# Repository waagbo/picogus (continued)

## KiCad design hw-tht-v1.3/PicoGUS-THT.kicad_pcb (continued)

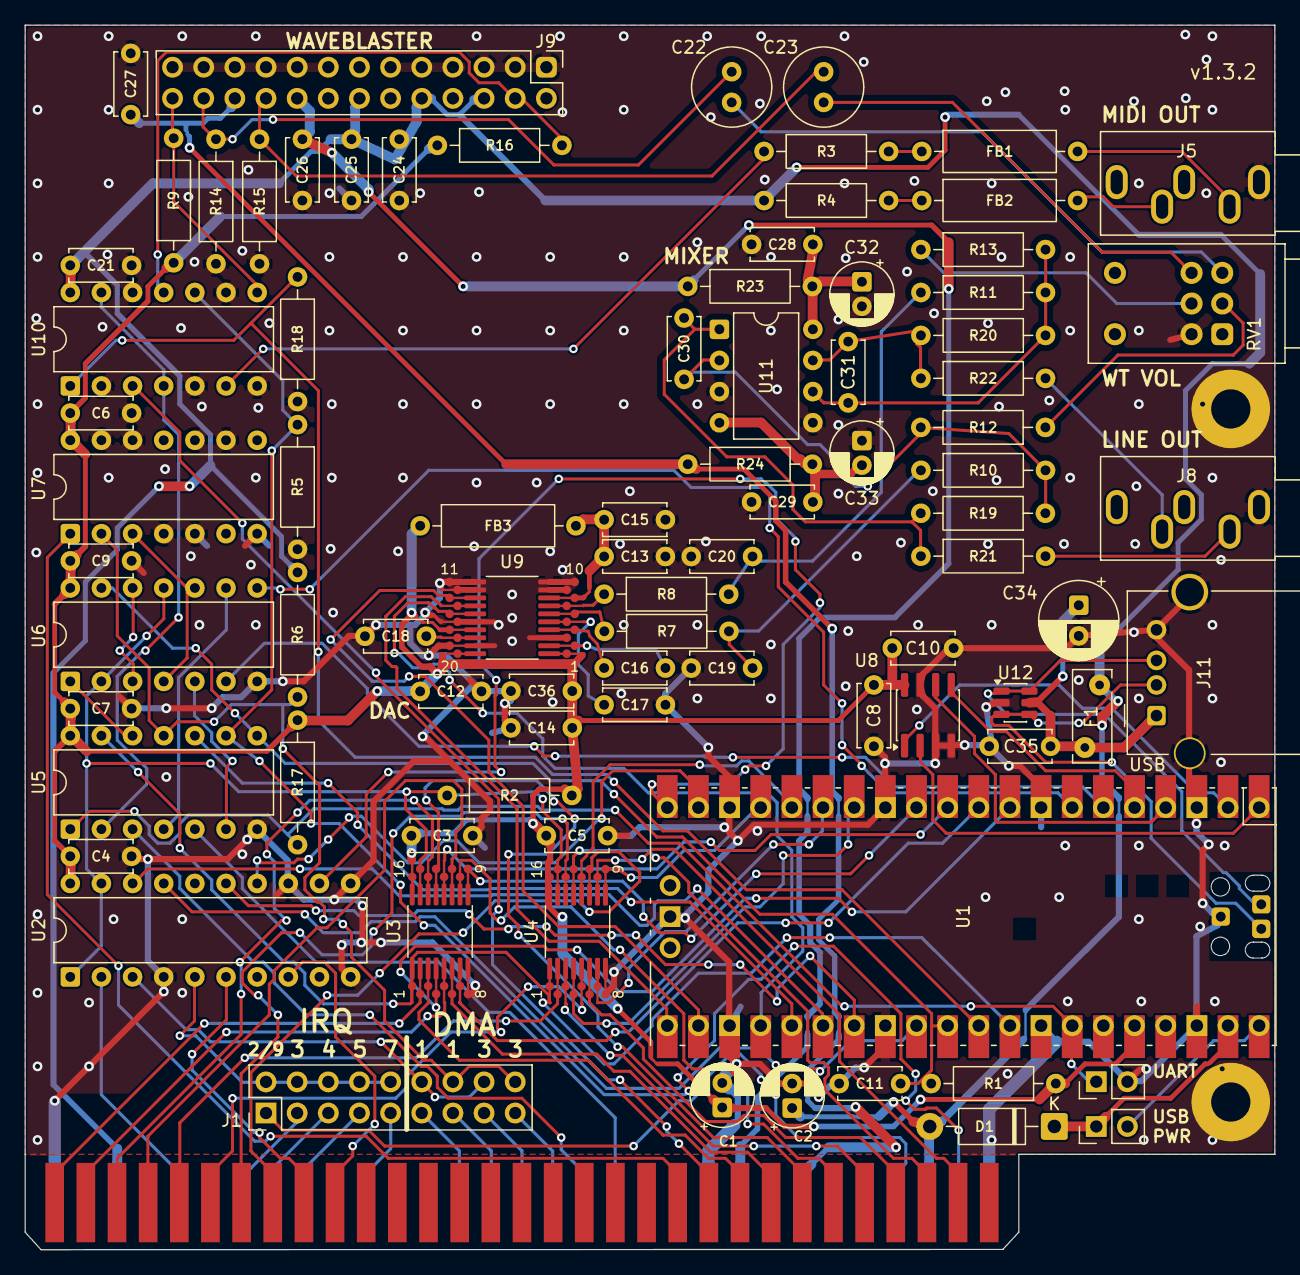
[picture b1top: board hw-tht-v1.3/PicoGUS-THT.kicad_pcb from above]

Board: 2 copper layers, 101.9 x 99.8 mm, 88 parts (0 on the bottom side), 110 nets.

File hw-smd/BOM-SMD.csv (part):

References,Qty,Value,Type,Footprint,Manufacturer,MPN,DigiKey PN,DigiKey link,DigiKey stock 2026-09-29,Unit NOK (1 board),Line NOK (1 board),Alternatives,Notes
U1,1,Raspberry Pi Pico,THT module,RPi_Pico_SMD_TH,Raspberry Pi,SC0915,2648-SC0915CT-ND,https://www.digikey.no/no/products/result?keywords=2648-SC0915CT-ND,42851,44.05,44.05,"Pico H SC0917 (DK 2648-SC0917-ND, 8889; JLCPCB lib C21351132). Pico W also works.","LCSC: Pico is only in the JLCPCB assembly parts library, not the LCSC shop - buy from DigiKey or an approved Raspberry Pi reseller. Solder on 2x 1x20 male headers (from the 1x40 strip) or socket it."
U2,1,74LVC244,SMD TSSOP-20,TSSOP-20_4.4x6.5mm_P0.65mm,Texas Instruments,SN74LVC244APW,296-26609-5-ND,https://www.digikey.no/no/products/result?keywords=296-26609-5-ND,2154,11.61,11.61,"Nexperia 74LVC244APW,118 (v1.2 BOM, DK 1727-2875-1-ND, 0 in stock today).",
"U3, U4",2,SN74CB3T3257,SMD TSSOP-16,TSSOP-16_4.4x5mm_P0.65mm,Texas Instruments,SN74CB3T3257PWR,296-17850-1-ND,https://www.digikey.no/no/products/result?keywords=296-17850-1-ND,4031,19.96,39.93,,TSSOP-16. No DIP or SOIC version exists (only PW/DGV).
U5,1,74AHC14,SMD SOIC-14,SOIC-14_3.9x8.7mm_P1.27mm,Diodes Inc,74AHC14S14-13,31-74AHC14S14-13CT-ND,https://www.digikey.no/no/products/result?keywords=31-74AHC1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,3070,3.55,3.55,,"Must be 74AHC14 (higher Schmitt threshold, see v1.2 changelog)."
U6,1,74LVC00,SMD SOIC-14,SOIC-14_3.9x8.7mm_P1.27mm,Diodes Inc,74LVC00AS14-13,31-74LVC00AS14-13CT-ND,https://www.digikey.no/no/products/result?keywords=31-74LVC0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,1816,3.65,3.65,,
U7,1,74LVC1G00,SMD SOT-23-5,SOT-23-5,Texas Instruments,SN74LVC1G00DBVR,296-9845-1-ND,https://www.digikey.no/no/products/result?keywords=296-9845-1-ND,14500,1.34,1.34,,
U8,1,APS6404L-3SQR-SN,SMD SOIC-8,SOIC-8_3.9x4.9mm_P1.27mm,AP Memory,APS6404L-3SQR-SN [Adafruit 4677 (64Mbit QSPI PSRAM)],1528-4677-ND,https://www.digikey.no/no/products/result?keywords=1528-4677-ND,4132,16.80,16.80,,SOIC-8. DigiKey does not stock the APS6404L itself; Adafruit 4677 is the DigiKey source (as in v1.2). Note: v1.2 BOM LCSC C139966 is actually a Vilsion VTI7064MSME (compatible).
U9,1,PCM5100A,SMD TSSOP-20,TSSOP-20_4.4x6.5mm_P0.65mm,Texas Instruments,PCM5100APWR,296-36705-1-ND,https://www.digikey.no/no/products/result?keywords=296-36705-1-ND,1419,25.15,25.15,"Pin-compatible PCM5102APWR (DK 296-36707-1-ND 619, LCSC C107671 6471) or PCM5101APWR.","TSSOP-20, no THT version exists. DAC AREA: leave out U9, C12-C20, FB3, R7 and R8 when the GY-PCM5102 module (J10) is fitted instead."
J10,1,GY-PCM5102 module,"THT (optional, instead of the DAC area)",GY-PCM5102_Module,generic,GY-PCM5102,,,,,,,"OPTION: replaces U9 + C12-C20 + FB3 + R7/R8 - exactly the parts under the dashed J10 module outline (the module has the same 470R/2.2nF output filter). Fit ONE of the two, never both. Not sold by DigiKey (AliExpress/eBay etc). Solder it almost flat, directly on 2.54 mm male pins: its 6-pin I2S header and a 4-pin piece of the 1x40 strip on AGND/ROUT/AGND/LROUT. No sockets: raised on 8.5 mm sockets it would hit a Waveblaster daughterboard. Set its solder jumpers H1=L H2=L H3=H H4=L."
"U10, U12",2,74LVC2G06,SMD SOT-23-6,TSOP-6_1.65x3.05mm_P0.95mm,Texas Instruments,SN74LVC2G06DBVR,296-13492-1-ND,https://www.digikey.no/no/products/result?keywords=296-13492-1-ND,25644,3.46,6.91,,Open-drain inverters. U10: IOCHRDY + MIDI out (as v1.2). U12: Waveblaster /RESET + MIDI (new).
U11,1,NE5532,SMD SOIC-8,SOIC-8_3.9x4.9mm_P1.27mm,Texas Instruments,NE5532DR,296-13622-1-ND,https://www.digikey.no/no/products/result?keywords=296-13622-1-ND,50117,4.80,4.80,,WT/PCM summing amplifier on the (filtered) ISA +/-12 V.
D1,1,B5819W,SMD SOD-123,D_SOD-123,Slkor (Shenzhen Slkormicro),B5819W,5399-B5819WCT-ND,https://www.digikey.no/no/products/result?keywords=5399-B5819WCT-ND,67294,2.69,2.69,,"40 V 1 A Schottky, SOD-123 (cut tape; 5399-B5819WTR-ND is a 3000-pc reel). Replaces MCC B5819W-TP (purchase-limited at DigiKey); Comchip CDBW140-G (641-1458-1-ND) also fits. JLCPCB assembly keeps B5819W (LCSC C84354)."
"C1, C2",2,47uF,SMD 1206,C_1206_3216Metric,TDK,C3216X5R1A476M160AB,445-6006-1-ND,https://www.digikey.no/no/products/result?keywords=445-6006-1-ND,33669,7.97,15.93,v1.2 Samsung CL31A476MPHNNNE (0 at DigiKey today).,
"C3, C4, C5, C6, C7, C8, C9, C11, C12, C13, C14, C18, C21, C25, C26, C27, C28, C29",18,0.1uF,SMD 0805,C_0805_2012Metric,Samsung,CL21B104KBCNNNC,1276-1003-1-ND,https://www.digikey.no/no/products/result?keywords=1276-1003-1-ND,4889645,0.43,7.77,,50V X7R.
C10,1,1uF,SMD 0805,C_0805_2012Metric,TDK,C2012X7R1H105K125AB,445-7547-1-ND,https://www.digikey.no/no/products/result?keywords=445-7547-1-ND,7594,2.88,2.88,,50V X7R.
"C15, C24",2,10uF,SMD 1206,C_1206_3216Metric,Samsung,CL31A106KAHNNNE,1276-1075-1-ND,https://www.digikey.no/no/products/result?keywords=1276-1075-1-ND,18634,2.11,4.22,"TDK C3216X5R1E106K160AB (DK 445-6862-1-ND, 43950).",25V X5R. 1206 because no 10uF 0805 is in stock at DigiKey today.
"C16, C17",2,2.2uF,SMD 0805,C_0805_2012Metric,TDK,C2012X7R1H225K125AC,445-5968-1-ND,https://www.digikey.no/no/products/result?keywords=445-5968-1-ND,499706,5.09,10.17,,50V X7R.
"C19, C20",2,2.2nF C0G,SMD 0805,C_0805_2012Metric,Samsung,CL21C222JBFNNNE,1276-2993-1-ND,https://www.digikey.no/no/products/result?keywords=1276-2993-1-ND,51757,1.34,2.69,,C0G/NP0 (DAC output filter). DAC AREA: leave out with the GY-PCM5102 module (J10).
"C30, C31",2,47pF C0G,SMD 0805,C_0805_2012Metric,Samsung,CL21C470JC61PNC,1276-6521-1-ND,https://www.digikey.no/no/products/result?keywords=1276-6521-1-ND,67127,1.70,3.40,,"C0G/NP0 (op-amp feedback), 100 V. Previous value: 100pF C0G (Samsung CL21C101JBANNNC). 47 pF with the 20k feedback keeps the feedback pole at ~170 kHz. JLCPCB/LCSC: C14857 (CL21C470JBANNNC, 50 V; DigiKey does not stock it). Stock checked 2026-10-09."
"C22, C23",2,10uF bipolar,SMD 6.3x5.4,CP_Elec_6.3x5.4,Panasonic,EEE-1EA100NP,PCE4294CT-ND,https://www.digikey.no/no/products/result?keywords=PCE4294CT-ND,6070,6.05,12.09,"Nichicon UUP1V100MCL1GS (bipolar 35V, DK 493-9559-1-ND, 3792).",WT audio coupling: NON-POLAR electrolytic (either orientation). The footprint shows a + mark only because KiCad has no non-polar SMD electrolytic footprint.
"C32, C33",2,47uF 35V,SMD 6.3x7.7,CP_Elec_6.3x7.7,Panasonic,EEE-FK1V470P,PCE3842CT-ND,https://www.digikey.no/no/products/result?keywords=PCE3842CT-ND,47922,6.24,12.48,,Op-amp +/-12 V RC filter. C33: + to GND.
"FB1, FB2, FB3",3,1k@100MHz,SMD 0805,L_0805_2012Metric,Murata,BLM21AG102SN1D,490-1041-1-ND,https://www.digikey.no/no/products/result?keywords=490-1041-1-ND,621156,1.54,4.61,,FB1/FB2: MIDI out EMI. FB3: DAC AVDD filter.
R1,1,1k,SMD 0805,R_0805_2012Metric,Yageo,RC0805FR-071KL,311-1.00KCRCT-ND,https://www.digikey.no/no/products/result?keywords=311-1.00KCRCT-ND,732526,0.96,0.96,,
"R2, R5, R6",3,15k,SMD 0805,R_0805_2012Metric,Yageo,RC0805FR-0715KL,311-15.0KCRCT-ND,https://www.digikey.no/no/products/result?keywords=311-15.0KCRCT-ND,127426,0.96,2.88,,
"R3, R4",2,220R,SMD 0805,R_0805_2012Metric,Yageo,RC0805FR-07220RL,311-220CRCT-ND,https://www.digikey.no/no/products/result?keywords=311-220CRCT-ND,420320,0.96,1.92,,
"R7, R8",2,470R 0.1% thin film,SMD 0805,R_0805_2012Metric,Yageo,RT0805BRD07470RL,YAG1904CT-ND,https://www.digikey.no/no/products/result?keywords=YAG1904CT-ND,12924,1.06,2.11,,"Thin film in the audio path (lower noise and voltage coefficient than thick film). DAC output filter: leave out with the GY-PCM5102 module (J10), which has the same filter."
"R12, R13",2,10k 0.1% thin film,SMD 0805,R_0805_2012Metric,Yageo,RT0805BRD0710KL,YAG1763CT-ND,https://www.digikey.no/no/products/result?keywords=YAG1763CT-ND,176155,0.96,1.92,,"Mixer WT inputs: thin film, 0.1% keeps the L/R gains matched. Until 2026-10-09 this line also held R10, R11, R19, R20 (6 pcs); those are now 20k."
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
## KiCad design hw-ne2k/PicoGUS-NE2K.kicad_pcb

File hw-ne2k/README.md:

# PicoGUS NE2000 v1.0 – WiFi network card based on PicoGUS v1.2

A third card in this repository: the PicoGUS **v1.2** ISA interface with **everything audio removed**,
built around a **Raspberry Pi Pico W** so it runs the PicoGUS NE2000 firmware (`pg-ne2k`: an NE2000
that talks to the network over WiFi). Added:

* **USB-A host port** at the bracket, wired to the Pico W's USB test points (TP2/TP3), for USB mice,
  joysticks and storage (the same idea as the PicoGUS 2.0 USB-A port)
* **8 MB PSRAM** (APS6404L) kept, for buffering/caching in future firmware
* **Boot ROM** on the ISA memory bus: an in-system-writable SST39SF010A flash with 4 × 32 KB images
  (e.g. iPXE for PXE boot, a disk-image boot ROM, XT-IDE BIOS), configured from the Pico W

> **Status: prototype design, not yet fabricated or tested.** The schematic passes ERC (no errors
> beyond those inherited from v1.2). The board was autorouted and checked with DRC in KiCad 10:
> **0 errors, 0 unconnected**, and it matches the schematic. Firmware support for the boot ROM
> (enable/base/bank set-up, ROM images, flashing tool) does not exist yet; the stock `pg-ne2k` firmware
> runs the NE2000 and leaves the ROM switched off.

| File | What |
|---|---|
| `PicoGUS-NE2K.kicad_pro/.kicad_sch/.kicad_pcb` | KiCad **10** project. Root sheet: the v1.2 ISA logic + Pico W + PSRAM |
| `bootrom.kicad_sch` | Boot ROM (U13–U16) and USB-A host port (J5, U17, F1) |
| `PicoGUS-NE2K-schematic.pdf` | Schematic PDF |
| `BOM-NE2K.csv` | BOM with a **DigiKey link** for every line, stock and NOK price |
| `BOM-NE2K-digikey-upload.csv` / `-10x.csv` | DigiKey cart/BOM upload for 1 / 10 boards (designators as Customer Reference) |
| `build/jlcpcb/` | Gerbers, drill, assembly BOM and placement files for JLCPCB (regenerate with `hw-common/tools/jlcpcb.sh`) |

## What is on the card

### Kept from v1.2 (unchanged)

U2 74LVC244, U3/U4 SN74CB3T3257, U5 74AHC14, U6 74LVC00, U7 74LVC1G00, U8 APS6404L PSRAM and
U10A 74LVC2G06 (IOCHRDY), with the same Pico GPIO assignment as v1.2. So the stock PicoGUS firmware
builds (`pg-ne2k`, the USB mouse/joystick build, `multifw`) work without changes; the sound modes of
`multifw` simply have no DAC to play through.

### Removed

* **Audio:** PCM510x DAC, the GY-PCM5102 option, line-out and the Waveblaster/mixer section of v1.3
* **MIDI out** (J5 jack, R3/R4, FB1/FB2). U10B stays on the board (its input is still driven) with the
  output unconnected.
* **ISA DMA:** the DRQ/DACK jumpers and the DRQ/DACK/TC paths. The NE2000 moves packet data with
  programmed I/O through its data port (its "remote DMA" is internal to the NE2000, not ISA DMA), so
  `pg-ne2k` never uses DRQ or DACK. DACK keeps its pull-up (R6), so the AEN gating (U7) works as before.
* **J7 (USB power jumper):** the USB-A port has its own VBUS supply.

### IRQ (J1)

J1 is now a **2×5 header**: one jumper selects **IRQ 2/9, 3, 4, 5 or 7** for the NE2000 (same layout as
the IRQ half of the v1.2 J1). IRQ 3 is the usual NE2000 choice if COM2 is not used.

### Pico W, antenna and USB-A

* **U1 must be a Pico W** (SC0918). The NE2000 firmware is built for the RP2040 + CYW43439; a
  Pico 2 W does not work.
* **Solder the Pico W flat** (castellated edges, or pins cut flush), not on header pins: the USB data
  lines are taken from its **TP2 (D−) and TP3 (D+)** test points on the underside. The footprint
  (`RPi_PicoW_SMD_TH_USB`) has plated 1.5 mm pads with a 0.6 mm hole there, so you solder them from the
  back of the card after the module is in place. TP1 (USB ground) is connected the same way. A Pico WH
  (pre-soldered headers) cannot be used.
* **The antenna end points at the bracket**, as far out as the board allows. No copper on either layer
  under the antenna (datasheet keep-out, 14 × 9 mm between the pin rows) or between the module end and
  the bracket edge. The footprint also drops the Pico's SWD pads, which would sit under the Pico W
  antenna.
* **USB-A (J5, Molex 67643)** sits at the bracket below the antenna, on the line of the v1.2 line-out jack.
  D+/D− run straight from the Pico's test points (the Pico's own 27 Ω series resistors are before them),
  with a USBLC6-2SC6 ESD protector (U17). VBUS comes from the ISA +5 V through a 0.5 A polyfuse (F1)
  with 10 µF + 0.1 µF. The Pico's own VBUS pin is not connected, so a PC on the micro-USB port (on the
  bench, for flashing) and the ISA supply never feed each other.
* **Firmware updates** go over ISA with `pgusinit` as usual. The micro-USB socket now faces into the card;
  it is still usable with the card out of the PC (BOOTSEL on the Pico).

### Boot ROM (bootrom.kicad_sch)

A real option ROM on the ISA memory bus, so the BIOS finds and runs it during POST.

* **U13 SST39SF010A** (128 KB, 5 V, PLCC-32), read through a **32 KB window**: SA0–SA14 go straight to the
  flash. Flash A15/A16 are the **bank** bits from the Pico, so the chip holds **4 images of 32 KB**.
* **U14 74HCT688** compares SA19..SA15 with `1 1 BASE2 BASE1 BASE0` and requires **ROM_EN = 1**. Its
  enable is `~MEMSTB` (U16: low during any ISA memory read or write), so the output `~ROM_CS` is only
  active in a memory cycle inside the window.
* **U15 74AHCT245** drives the flash data onto the ISA data bus (the flash alone is too weak for a loaded
  bus). Direction comes from `~SMEMW`, enable from `~ROM_CS`.
* **Base address** (BASE2..0): `001` C8000, `010` D0000, `011` D8000, `100` E0000, `101` E8000.
* **ROM_EN, BASE0–2, BANK0–1 are Pico GPIOs** (the pins freed by removing I2S and DMA):

  | GPIO | Pico pin | Signal |
  |---|---|---|
  | 16 | 21 | ROM_EN (pulled low by R3: ROM off until the firmware enables it) |
  | 17 | 22 | ROM_BASE0 |
  | 18 | 24 | ROM_BASE1 |
  | 19 | 25 | ROM_BASE2 |
  | 20 | 26 | ROM_BANK0 |
  | 22 | 29 | ROM_BANK1 |

  The firmware should set them from its stored settings first thing after reset. The Pico is running
  within tens of milliseconds of ISA RESET, while the BIOS scans for option ROMs only after its memory
  test. With the stock firmware the ROM stays invisible.
* **Writing the ROM from DOS:** fit **J2** (write enable: `~SMEMW` → flash WE#, R4 holds WE# high
  otherwise), then use the SST software command sequence (5555h/2AAAh lie inside the 32 KB window).
  Remove J2 afterwards.
* **What to put in the banks:** iPXE built with its `ne2k_isa` driver (PXE boot; iPXE needs a 386 or
  later), a small INT 13h ROM that boots a disk image the Pico fetches over WiFi (cached in the PSRAM; works
  on an 8088), or an XT-IDE BIOS. All of this is firmware work; the hardware only provides the ROM.

## Card dimensions and bracket

The card uses the **v1.2 outline: 103.7 × 74.2 mm** (bracket edge to far edge × fingers to top), with the
v1.2 edge connector and bracket holes H1/H2, so a v1.2 bracket screws on. The bracket needs:

* a **large opening in front of the antenna** (around the old MIDI-jack hole, y ≈ 80 mm on the board):
  metal close to the antenna is what costs range,
* a **USB-A cut-out** (about 14 × 7 mm) centred on the old line-out jack hole.

### Silkscreen

Front: IRQ numbers at J1, `ROM WE` at J2, `TX GND` at J6, `USB`, `WiFi ANTENNA` at the antenna end,
`REAR >`. Back: the PicoGUS artwork (`hw-common/art/picogus-artwork.svg`, 70 × 25 mm) over the lower half,
the dedication *This version is dedicated to Mila and Alisa, my two wonderful princesses, who fill my
world with joy.* behind the Pico, and the copyright/licence text (CERN-OHL-P v2).

## Building it

* Everything except U1, J1, J2, J5, J6 and the jumpers is SMD on the top side. `hw-common/tools/jlcpcb.sh
  hw-ne2k/PicoGUS-NE2K.kicad_pcb` writes gerbers, drill, assembly BOM and placement files to `build/jlcpcb/`
  (38 SMD placements). The parts have no LCSC numbers yet, so pick them in JLCPCB's part matcher (or order
  the parts from DigiKey and assemble by hand).
* Solder the **Pico W flat**, then solder **TP1, TP2, TP3 from the back** through the plated holes.
* Jumpers: one on J1 (IRQ). J2 only while writing the boot ROM.
* Firmware: flash `pg-ne2k` (or `multifw`) with `pgusinit`, then set the WiFi SSID/password and the NE2000
  base port with `pgusinit` as on any PicoGUS.

## Ordering

`BOM-NE2K.csv` lists a DigiKey part for every line with stock and price (new parts checked on
digikey.com on 2026-10-05; parts shared with the SMD board from its 2026-09-29 check).
DigiKey parts only (no PCB, no shipping): **about 264 kr excl. MVA (~330 kr incl. 25 % MVA, ~$28) per
board**; the Pico W (73 kr), the PLCC flash (19 kr), the USB-A connector (18 kr) and the two bus switches
(20 kr) are the largest items.

## Sources

* PicoGUS v1.2 schematic (`hw/`) and the v1.3.0 SMD root sheet (`hw-smd/`)
* Raspberry Pi Pico W datasheet (test points TP1–TP6, SMT footprint, antenna keep-out)
* Microchip SST39SF010A datasheet; TI CD74HCT688, SN74AHCT245, SN74AHCT1G08 datasheets
* PicoGUS firmware: `sw/ne2000play.cpp`, `sw/ne2000/ne2000.c`, `sw/CMakeLists.txt` (`NE2K` target)

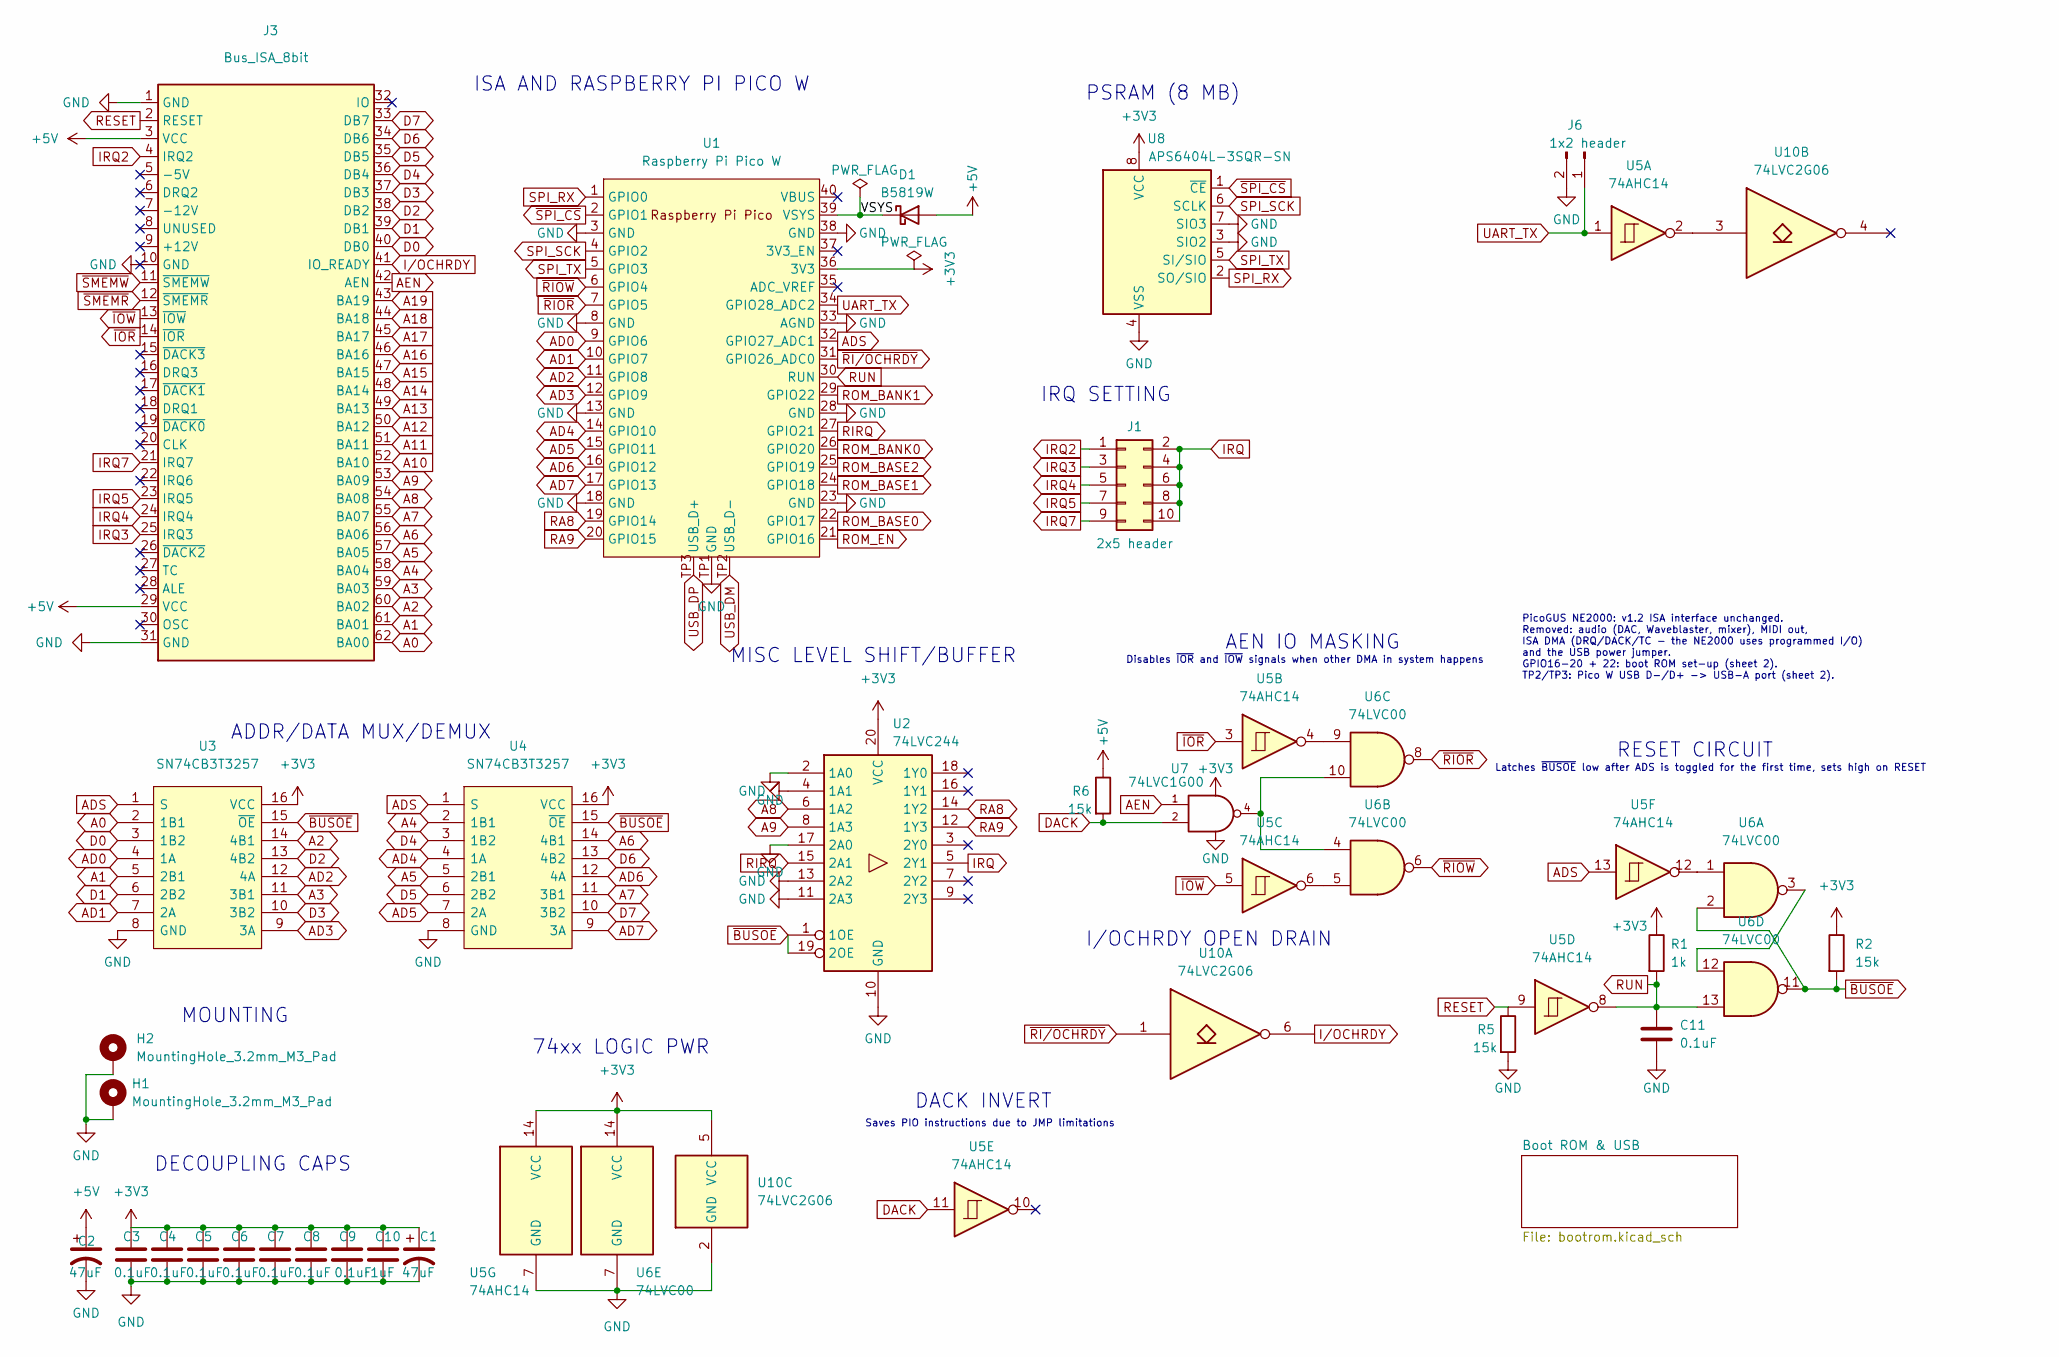
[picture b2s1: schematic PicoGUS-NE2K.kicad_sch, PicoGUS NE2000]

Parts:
C1, C2: 47uF; C_1206_3216Metric; MPN C3216X5R1A476M160AB; DigiKey 445-6006-1-ND
C3, C4, C5, C6, C7, C8, C9, C11: 0.1uF; C_0805_2012Metric; MPN CL21B104KBCNNNC; DigiKey 1276-1003-1-ND
C10: 1uF; C_0805_2012Metric; MPN C2012X7R1H105K125AB; DigiKey 445-7547-1-ND
D1: B5819W; D_SOD-123; MPN B5819W; DigiKey 5399-B5819WCT-ND
H1, H2: MountingHole_3.2mm_M3_Pad
J1: 2x5 header; PinHeader_2x05_P2.54mm_Vertical; MPN 10129381-910001BLF; DigiKey 10129381-910001BLF-ND
J3: Bus_ISA_8bit; BUS_PC_chamfer
J6: 1x2 header; PinHeader_1x02_P2.54mm_Vertical; MPN 77311-118-02LF; DigiKey 609-4434-ND
R1: 1k; R_0805_2012Metric; MPN RC0805FR-071KL; DigiKey 311-1.00KCRCT-ND
R2, R5, R6: 15k; R_0805_2012Metric; MPN RC0805FR-0715KL; DigiKey 311-15.0KCRCT-ND
U1: Raspberry Pi Pico W; RPi_PicoW_SMD_TH_USB; MPN SC0918; DigiKey 2648-SC0918CT-ND
U2: 74LVC244; TSSOP-20_4.4x6.5mm_P0.65mm; MPN SN74LVC244APW; DigiKey 296-26609-5-ND
U3, U4: SN74CB3T3257; TSSOP-16_4.4x5mm_P0.65mm; MPN SN74CB3T3257PWR; DigiKey 296-17850-1-ND
U5: 74AHC14; SOIC-14_3.9x8.7mm_P1.27mm; MPN 74AHC14S14-13; DigiKey 31-74AHC14S14-13CT-ND
U6: 74LVC00; SOIC-14_3.9x8.7mm_P1.27mm; MPN 74LVC00AS14-13; DigiKey 31-74LVC00AS14-13CT-ND
U7: 74LVC1G00; SOT-23-5; MPN SN74LVC1G00DBVR; DigiKey 296-9845-1-ND
U8: APS6404L-3SQR-SN; SOIC-8_3.9x4.9mm_P1.27mm; MPN APS6404L-3SQR-SN; DigiKey 1528-4677-ND
U10: 74LVC2G06; TSOP-6_1.65x3.05mm_P0.95mm; MPN SN74LVC2G06DBVR; DigiKey 296-13492-1-ND

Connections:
+3V3: C1.1, C3.1, C4.1, C5.1, C6.1, C7.1, C8.1, C9.1, C10.1, R1.1, R2.1, U1.36 (3V3), U2.20 (VCC), U3.16 (VCC), U4.16 (VCC), U5.14 (VCC), U6.14 (VCC), U7.5 (VCC), U8.8 (VCC), U10.5 (VCC)
+5V: C2.1, D1.2 (A), J3.3 (VCC), J3.29 (VCC), R6.1; also elsewhere on the board
/VSYS: D1.1 (K), U1.39 (VSYS)
A0: J3.62 (BA00), U3.2 (1B1); also elsewhere on the board
A1: J3.61 (BA01), U3.5 (2B1); also elsewhere on the board
A2: J3.60 (BA02), U3.14 (4B1); also elsewhere on the board
A3: J3.59 (BA03), U3.11 (3B1); also elsewhere on the board
A4: J3.58 (BA04), U4.2 (1B1); also elsewhere on the board
A5: J3.57 (BA05), U4.5 (2B1); also elsewhere on the board
A6: J3.56 (BA06), U4.14 (4B1); also elsewhere on the board
A7: J3.55 (BA07), U4.11 (3B1); also elsewhere on the board
A8: J3.54 (BA08), U2.6 (1A2); also elsewhere on the board
A9: J3.53 (BA09), U2.8 (1A3); also elsewhere on the board
A10: J3.52 (BA10); also elsewhere on the board
A11: J3.51 (BA11); also elsewhere on the board
A12: J3.50 (BA12); also elsewhere on the board
A13: J3.49 (BA13); also elsewhere on the board
A14: J3.48 (BA14); also elsewhere on the board
A15: J3.47 (BA15); also elsewhere on the board
A16: J3.46 (BA16); also elsewhere on the board
A17: J3.45 (BA17); also elsewhere on the board
A18: J3.44 (BA18); also elsewhere on the board
A19: J3.43 (BA19); also elsewhere on the board
AD0: U1.9 (GPIO6), U3.4 (1A)
AD1: U1.10 (GPIO7), U3.7 (2A)
AD2: U1.11 (GPIO8), U3.12 (4A)
AD3: U1.12 (GPIO9), U3.9 (3A)
AD4: U1.14 (GPIO10), U4.4 (1A)
AD5: U1.15 (GPIO11), U4.7 (2A)
AD6: U1.16 (GPIO12), U4.12 (4A)
AD7: U1.17 (GPIO13), U4.9 (3A)
ADS: U1.32 (GPIO27_ADC1), U3.1 (S), U4.1 (S), U5.13
AEN: J3.42 (AEN), U7.1
D0: J3.40 (DB0), U3.3 (1B2); also elsewhere on the board
D1: J3.39 (DB1), U3.6 (2B2); also elsewhere on the board
D2: J3.38 (DB2), U3.13 (4B2); also elsewhere on the board
D3: J3.37 (DB3), U3.10 (3B2); also elsewhere on the board
D4: J3.36 (DB4), U4.3 (1B2); also elsewhere on the board
D5: J3.35 (DB5), U4.6 (2B2); also elsewhere on the board
D6: J3.34 (DB6), U4.13 (4B2); also elsewhere on the board
D7: J3.33 (DB7), U4.10 (3B2); also elsewhere on the board
DACK: R6.2, U5.11, U7.2
GND: C1.2, C2.2, C3.2, C4.2, C5.2, C6.2, C7.2, C8.2, C9.2, C10.2, C11.2, H1.1, H2.1, J3.1 (GND), J3.10 (GND), J3.31 (GND), J6.2, R5.2, U1.3 (GND), U1.8 (GND), U1.13 (GND), U1.18 (GND), U1.23 (GND), U1.28 (GND), U1.33 (AGND), U1.38 (GND), U1.TP1 (GND), U2.2 (1A0), U2.4 (1A1), U2.10 (GND), U2.11 (2A3), U2.13 (2A2), U2.17 (2A0), U3.8 (GND), U4.8 (GND), U5.7 (GND), U6.7 (GND), U7.3 (GND), U8.3 (SIO2), U8.4 (VSS), U8.7 (SIO3), U10.2 (GND); also elsewhere on the board
IRQ: J1.2, J1.4, J1.6, J1.8, J1.10, U2.5 (2Y1)
IRQ2: J1.1, J3.4 (IRQ2)
IRQ3: J1.3, J3.25 (IRQ3)
IRQ4: J1.5, J3.24 (IRQ4)
IRQ5: J1.7, J3.23 (IRQ5)
IRQ7: J1.9, J3.21 (IRQ7)
I/OCHRDY: J3.41 (IO_READY), U10.6
unnamed: U5.4, U6.9
unnamed: U5.6, U6.5
unnamed: U5.12, U6.1
unnamed: U6.4, U6.10, U7.4
unnamed: U6.3, U6.12
unnamed: U5.2, U10.3
RA8: U1.19 (GPIO14), U2.14 (1Y2)
RA9: U1.20 (GPIO15), U2.12 (1Y3)
RESET: J3.2 (RESET), R5.1, U5.9
RIRQ: U1.27 (GPIO21), U2.15 (2A1)
ROM_BANK0: U1.26 (GPIO20); also elsewhere on the board
ROM_BANK1: U1.29 (GPIO22); also elsewhere on the board
ROM_BASE0: U1.22 (GPIO17); also elsewhere on the board
ROM_BASE1: U1.24 (GPIO18); also elsewhere on the board
ROM_BASE2: U1.25 (GPIO19); also elsewhere on the board
ROM_EN: U1.21 (GPIO16); also elsewhere on the board
RUN: C11.1, R1.2, U1.30 (RUN), U5.8, U6.13
SPI_RX: U1.1 (GPIO0), U8.2 (SO/SIO)
SPI_SCK: U1.4 (GPIO2), U8.6 (SCLK)
SPI_TX: U1.5 (GPIO3), U8.5 (SI/SIO)
UART_TX: J6.1, U1.34 (GPIO28_ADC2), U5.1
USB_DM: U1.TP2 (USB_D-); also elsewhere on the board
USB_DP: U1.TP3 (USB_D+); also elsewhere on the board
~BUSOE: R2.2, U2.1 (1OE), U2.19 (2OE), U3.15 (~OE), U4.15 (~OE), U6.2, U6.11
~IOR: J3.14 (~IOR), U5.3
~IOW: J3.13 (~IOW), U5.5
~RIOR: U1.7 (GPIO5), U6.8
~RIOW: U1.6 (GPIO4), U6.6
~RI/OCHRDY: U1.31 (GPIO26_ADC0), U10.1
~SMEMR: J3.12 (~SMEMR); also elsewhere on the board
~SMEMW: J3.11 (~SMEMW); also elsewhere on the board
~SPI_CS: U1.2 (GPIO1), U8.1 (~CE)

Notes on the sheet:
Saves PIO instructions due to JMP limitations
DECOUPLING CAPS
Disables ~{IOR} and ~{IOW} signals when other DMA in system happens
Latches ~{BUSOE} low after ADS is toggled for the first time, sets high on RESET
MOUNTING
MISC LEVEL SHIFT/BUFFER
IRQ SETTING
DACK INVERT
ADDR/DATA MUX/DEMUX
PSRAM (8 MB)
AEN IO MASKING
ISA AND RASPBERRY PI PICO W
RESET CIRCUIT
I/OCHRDY OPEN DRAIN
74xx LOGIC PWR
PicoGUS NE2000: v1.2 ISA interface unchanged. Removed: audio (DAC, Waveblaster, mixer), MIDI out, ISA DMA (DRQ/DACK/TC - the NE2000 uses programmed I/O) and the USB power jumper. GPIO16-20 + 22: boot ROM set-up (sheet 2). TP2/TP3: Pico W USB D-/D+ -> USB-A port (sheet 2).

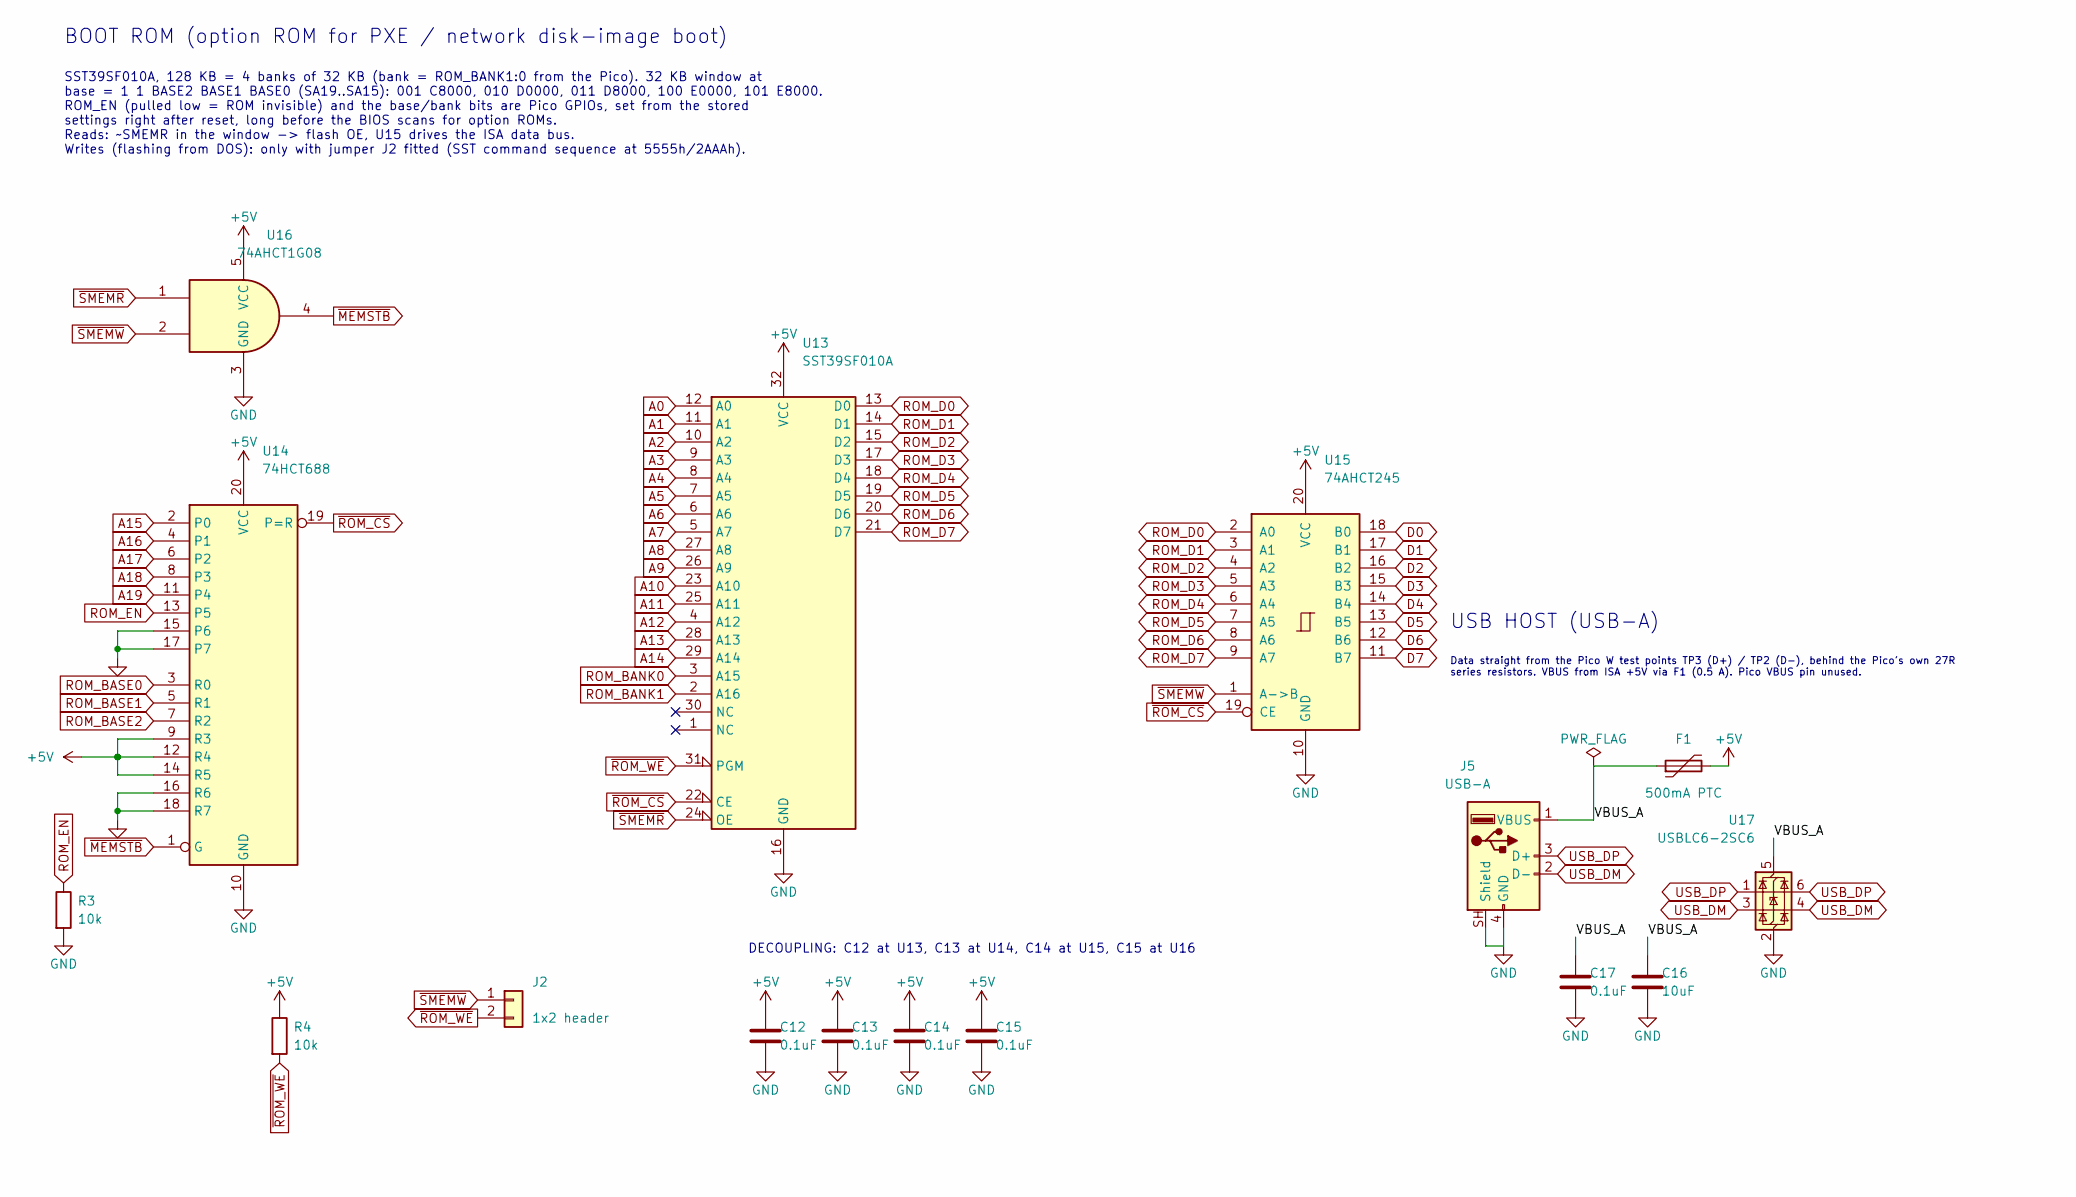
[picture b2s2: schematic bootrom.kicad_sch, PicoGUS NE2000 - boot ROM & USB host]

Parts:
C12, C13, C14, C15, C17: 0.1uF; C_0805_2012Metric; MPN CL21B104KBCNNNC; DigiKey 1276-1003-1-ND
C16: 10uF; C_1206_3216Metric; MPN CL31A106KAHNNNE; DigiKey 1276-1075-1-ND
F1: 500mA PTC; Fuse_1206_3216Metric; MPN MF-NSMF050-2; DigiKey MF-NSMF050-2CT-ND
J2: 1x2 header; PinHeader_1x02_P2.54mm_Vertical; MPN 77311-118-02LF; DigiKey 609-4434-ND
J5: USB-A; USB_A_Molex_67643_Horizontal; MPN 0676432910; DigiKey WM11258-ND
R3, R4: 10k; R_0805_2012Metric; MPN RC0805FR-0710KL; DigiKey 311-10.0KCRCT-ND
U13: SST39SF010A; PLCC-32_11.4x14.0mm_P1.27mm; MPN SST39SF010A-70-4C-NHE; DigiKey SST39SF010A-70-4C-NHE-ND
U14: 74HCT688; SOIC-20W_7.5x12.8mm_P1.27mm; MPN CD74HCT688M96; DigiKey 296-24357-1-ND
U15: 74AHCT245; TSSOP-20_4.4x6.5mm_P0.65mm; MPN SN74AHCT245PWR; DigiKey 296-1118-1-ND
U16: 74AHCT1G08; SOT-23-5; MPN SN74AHCT1G08DBVR; DigiKey 296-1113-1-ND
U17: USBLC6-2SC6; SOT-23-6; MPN USBLC6-2SC6; DigiKey 497-5235-1-ND

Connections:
+5V: C12.1, C13.1, C14.1, C15.1, F1.2, R4.1, U13.32 (VCC), U14.9 (R3), U14.12 (R4), U14.14 (R5), U14.20 (VCC), U15.20 (VCC), U16.5 (VCC); also elsewhere on the board
/Boot ROM & USB/VBUS_A: C16.1, C17.1, F1.1, J5.1 (VBUS), U17.5 (VBUS)
A0: U13.12 (A0); also elsewhere on the board
A1: U13.11 (A1); also elsewhere on the board
A2: U13.10 (A2); also elsewhere on the board
A3: U13.9 (A3); also elsewhere on the board
A4: U13.8 (A4); also elsewhere on the board
A5: U13.7 (A5); also elsewhere on the board
A6: U13.6 (A6); also elsewhere on the board
A7: U13.5 (A7); also elsewhere on the board
A8: U13.27 (A8); also elsewhere on the board
A9: U13.26 (A9); also elsewhere on the board
A10: U13.23 (A10); also elsewhere on the board
A11: U13.25 (A11); also elsewhere on the board
A12: U13.4 (A12); also elsewhere on the board
A13: U13.28 (A13); also elsewhere on the board
A14: U13.29 (A14); also elsewhere on the board
A15: U14.2 (P0); also elsewhere on the board
A16: U14.4 (P1); also elsewhere on the board
A17: U14.6 (P2); also elsewhere on the board
A18: U14.8 (P3); also elsewhere on the board
A19: U14.11 (P4); also elsewhere on the board
D0: U15.18 (B0); also elsewhere on the board
D1: U15.17 (B1); also elsewhere on the board
D2: U15.16 (B2); also elsewhere on the board
D3: U15.15 (B3); also elsewhere on the board
D4: U15.14 (B4); also elsewhere on the board
D5: U15.13 (B5); also elsewhere on the board
D6: U15.12 (B6); also elsewhere on the board
D7: U15.11 (B7); also elsewhere on the board
GND: C12.2, C13.2, C14.2, C15.2, C16.2, C17.2, J5.4 (GND), J5.SH (Shield), R3.2, U13.16 (GND), U14.10 (GND), U14.15 (P6), U14.16 (R6), U14.17 (P7), U14.18 (R7), U15.10 (GND), U16.3 (GND), U17.2 (GND); also elsewhere on the board
ROM_BANK0: U13.3 (A15); also elsewhere on the board
ROM_BANK1: U13.2 (A16); also elsewhere on the board
ROM_BASE0: U14.3 (R0); also elsewhere on the board
ROM_BASE1: U14.5 (R1); also elsewhere on the board
ROM_BASE2: U14.7 (R2); also elsewhere on the board
ROM_D0: U13.13 (D0), U15.2 (A0)
ROM_D1: U13.14 (D1), U15.3 (A1)
ROM_D2: U13.15 (D2), U15.4 (A2)
ROM_D3: U13.17 (D3), U15.5 (A3)
ROM_D4: U13.18 (D4), U15.6 (A4)
ROM_D5: U13.19 (D5), U15.7 (A5)
ROM_D6: U13.20 (D6), U15.8 (A6)
ROM_D7: U13.21 (D7), U15.9 (A7)
ROM_EN: R3.1, U14.13 (P5); also elsewhere on the board
USB_DM: J5.2 (D-), U17.3 (I/O2), U17.4 (I/O2); also elsewhere on the board
USB_DP: J5.3 (D+), U17.1 (I/O1), U17.6 (I/O1); also elsewhere on the board
~MEMSTB: U14.1 (G), U16.4
~ROM_CS: U13.22 (CE), U14.19 (P=R), U15.19 (CE)
~ROM_WE: J2.2, R4.2, U13.31 (PGM)
~SMEMR: U13.24 (OE), U16.1; also elsewhere on the board
~SMEMW: J2.1, U15.1 (A->B), U16.2; also elsewhere on the board

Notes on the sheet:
DECOUPLING: C12 at U13, C13 at U14, C14 at U15, C15 at U16
BOOT ROM (option ROM for PXE / network disk-image boot)
SST39SF010A, 128 KB = 4 banks of 32 KB (bank = ROM_BANK1:0 from the Pico). 32 KB window at base = 1 1 BASE2 BASE1 BASE0 (SA19..SA15): 001 C8000, 010 D0000, 011 D8000, 100 E0000, 101 E8000. ROM_EN (pulled low = ROM invisible) and the base/bank bits are Pico GPIOs, set from the stored settings right 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
USB HOST (USB-A)
Data straight from the Pico W test points TP3 (D+) / TP2 (D-), behind the Pico's own 27R series resistors. VBUS from ISA +5V via F1 (0.5 A). Pico VBUS pin unused.
